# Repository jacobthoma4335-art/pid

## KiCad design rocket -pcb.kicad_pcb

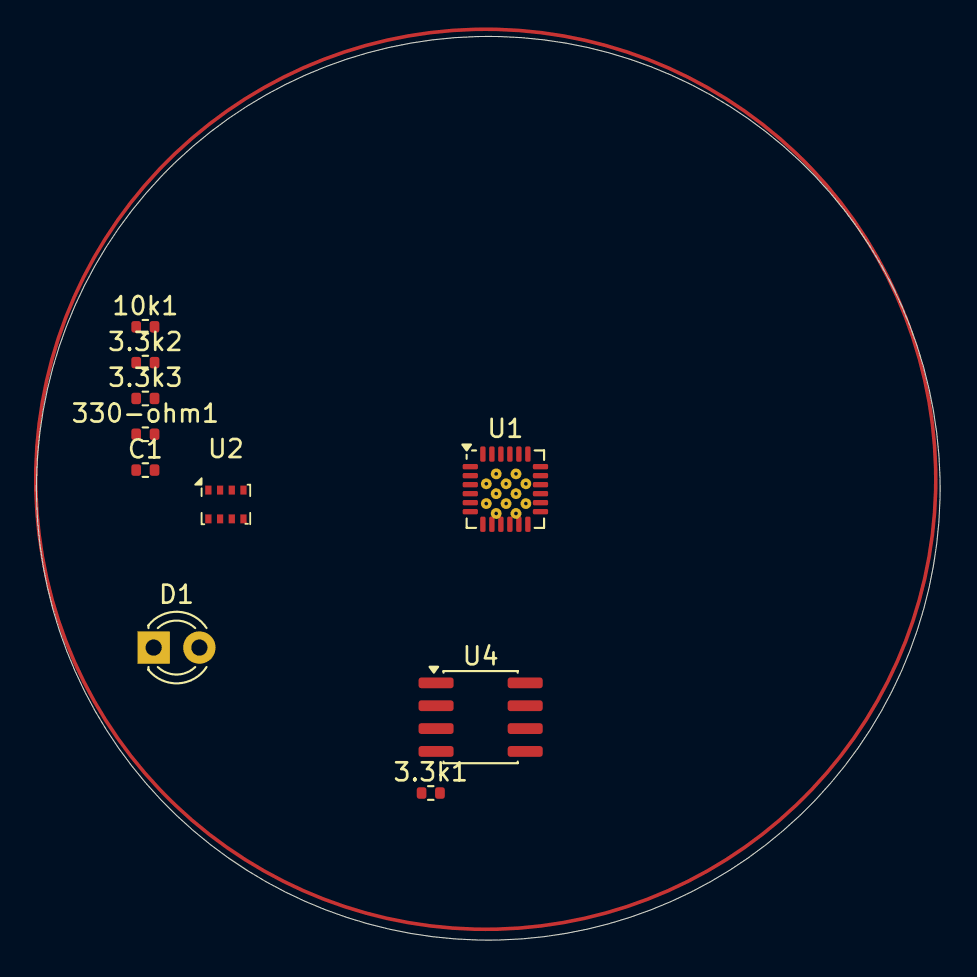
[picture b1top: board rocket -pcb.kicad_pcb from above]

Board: 2 copper layers, 50.2 x 50.2 mm, 11 parts (1 on the bottom side), 8 nets, no tracks yet.

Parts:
3.3k1, 3.3k2, 3.3k3, 10k1, 330-ohm1: R; R_0402_1005Metric
C1: C_Small_US; R_0402_1005Metric
D1: LED; LED_D3.0mm
U1: MPU-6050; InvenSense_QFN-24_4x4mm_P0.5mm
U2: BMP280; Bosch_LGA-8_2x2.5mm_P0.65mm_ClockwisePinNumbering
U3: ESP32-C3-WROOM-02
U4: CAT24C256; SOIC-8_3.9x4.9mm_P1.27mm

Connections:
+3.3V: 3.3k1.1, 3.3k2.2, 3.3k3.1, 10k1.2, C1.1, U1.13 (VDD), U2.2 (CSB), U2.8 (VDD), U3.1 (3V3), U4.8 (VCC)
GND: C1.2, D1.1 (K), U1.18 (GND), U2.1 (GND), U2.5 (SDO), U2.7 (GND), U3.9 (GND), U3.19 (GND), U4.4 (GND)
unnamed: 330-ohm1.2, D1.2 (A)
unnamed: 3.3k1.2, U1.23 (SCL), U2.3 (SDI), U3.4 (IO5), U4.6 (SCL)
unnamed: 3.3k2.1, U1.24 (SDA), U2.4 (SCK), U3.3 (IO4), U4.5 (SDA)
unnamed: 3.3k3.2, U3.2 (EN)
unnamed: 10k1.1, U3.7 (IO8), U3.8 (IO9), U3.16 (IO2)
unnamed: 330-ohm1.1, U3.15 (IO3)
